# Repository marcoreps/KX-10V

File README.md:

# KX-10V
Temperature controller and 10V buffer for xDevs KX LTZ1000 board

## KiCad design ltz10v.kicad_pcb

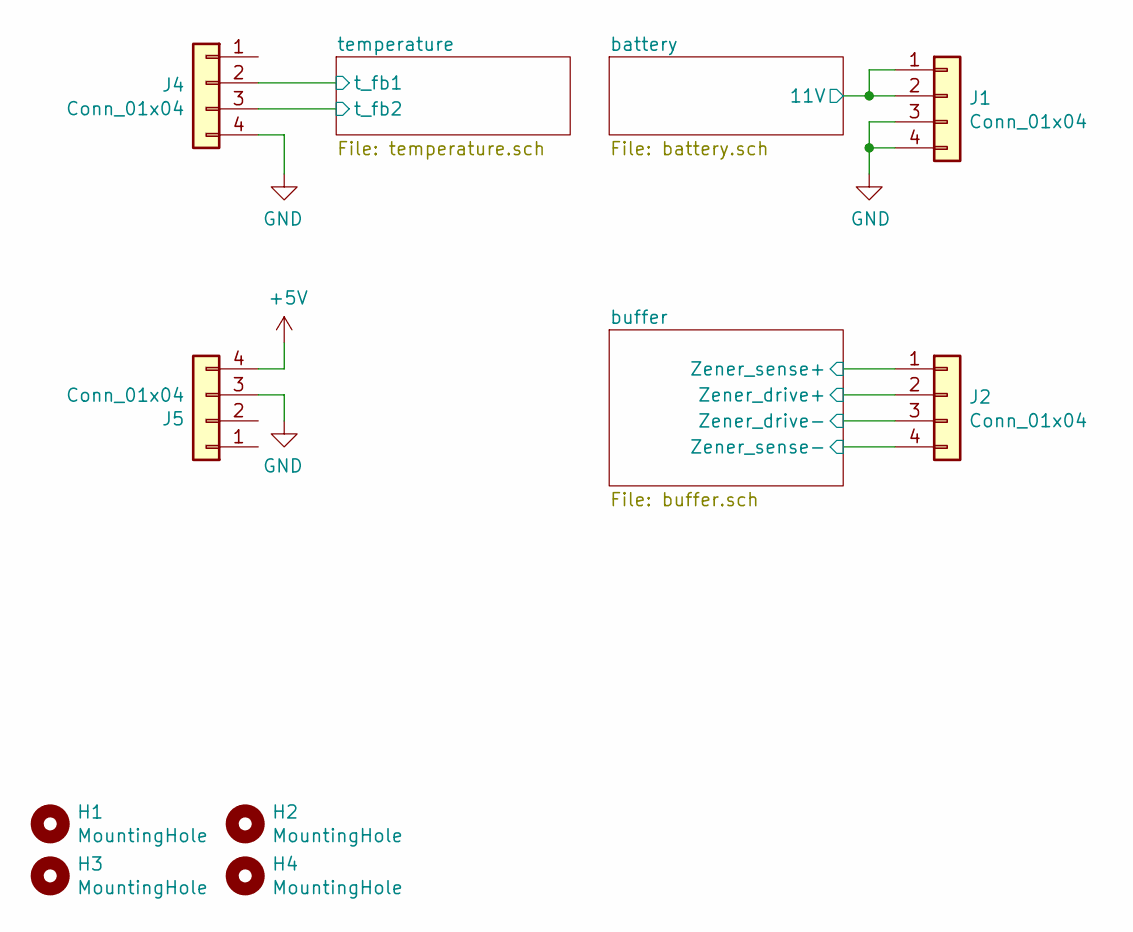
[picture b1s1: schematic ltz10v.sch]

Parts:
H1, H2, H3, H4: MountingHole; MountingHole_3.2mm_M3
J1, J2, J4, J5: Conn_01x04; PinHeader_1x04_P2.54mm_Vertical

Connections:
+5V: J5.4; also elsewhere on the board
/battery/11V: J1.1, J1.2; also elsewhere on the board
/buffer/Zener_drive+: J2.1, J2.2; also elsewhere on the board
/buffer/Zener_drive-: J2.3, J2.4; also elsewhere on the board
/temperature/t_fb1: J4.2; also elsewhere on the board
/temperature/t_fb2: J4.3; also elsewhere on the board
GND: J1.3, J1.4, J4.4, J5.3; also elsewhere on the board

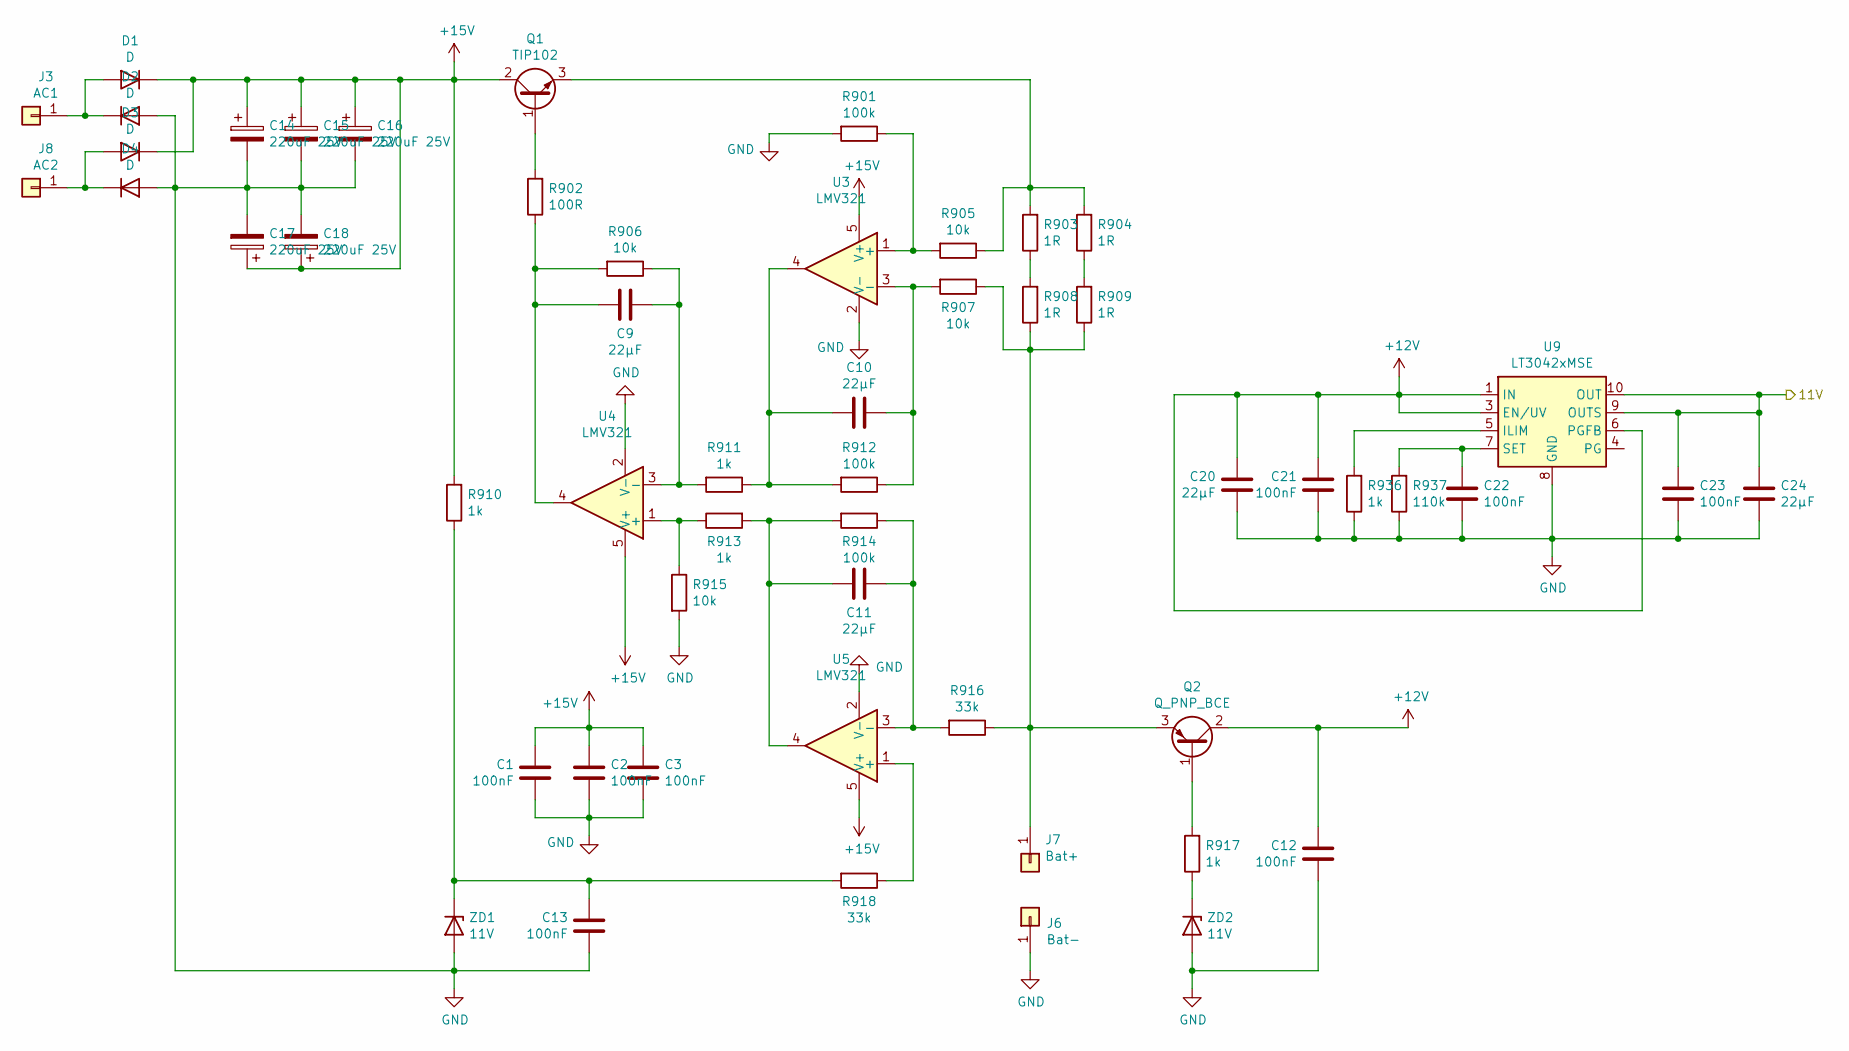
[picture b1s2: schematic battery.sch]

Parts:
C1, C2, C3, C12, C13, C21, C22, C23: 100nF; C_0805_2012Metric; LCSC C49678
C9, C10, C11, C20, C24: 22µF; C_0805_2012Metric; LCSC C45783
C14, C15, C16, C17, C18: 220uF 25V; CP_Elec_6.3x7.7
D1, D2, D3, D4: D; D_SMA; LCSC C8678
J3: AC1; SolderWirePad_1x01_Drill1.5mm
J6: Bat-; SolderWirePad_1x01_Drill1.5mm
J7: Bat+; SolderWirePad_1x01_Drill1.5mm
J8: AC2; SolderWirePad_1x01_Drill1.5mm
Q1: TIP102; TO-220-3_Vertical
Q2: Q_PNP_BCE; SOT-89-3; LCSC C24278
R901, R912, R914: 100k; R_0805_2012Metric; LCSC C17407
R902: 100R; R_0805_2012Metric; LCSC C17408
R903, R904, R908, R909: 1R; R_1206_3216Metric; LCSC C17928
R905, R906, R907, R915: 10k; R_0805_2012Metric; LCSC C17414
R910, R911, R913, R917, R936: 1k; R_0805_2012Metric; LCSC C17513
R916, R918: 33k; R_0805_2012Metric; LCSC C17633
R937: 110k; R_0805_2012Metric; LCSC C17422
U3, U4, U5: LMV321; SOT-23-5; LCSC C7972
U9: LT3042xMSE; MSOP-10-1EP_3x3mm_P0.5mm_EP1.68x1.88mm
ZD1, ZD2: 11V; D_SOD-323

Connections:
+12V: C12.1, C20.2, C21.1, Q2.2 (C), U9.1 (IN), U9.2 (IN), U9.3 (EN/UV), U9.6 (PGFB); also elsewhere on the board
+15V: C1.1, C2.1, C3.1, C14.1, C15.1, C16.1, C17.1, C18.1, D1.1 (K), D3.1 (K), Q1.2 (C), R910.2, U3.5 (V+), U4.5 (V+), U5.5 (V+)
/battery/11V: C23.1, C24.2, U9.9 (OUTS), U9.10 (OUT); also elsewhere on the board
GND: C1.2, C2.2, C3.2, C12.2, C13.2, C14.2, C15.2, C16.2, C17.2, C18.2, C20.1, C21.2, C22.2, C23.2, C24.1, D2.2 (A), D4.2 (A), J6.1, R901.2, R915.2, R936.1, R937.1, U3.2 (V-), U4.2 (V-), U5.2 (V-), U9.8 (GND), U9.11 (GND), ZD1.2 (A), ZD2.2 (A); also elsewhere on the board
unnamed: C9.1, R906.1, R911.2, U4.3 (-)
unnamed: C9.2, R902.1, R906.2, U4.4
unnamed: C10.1, R907.2, R912.1, U3.3 (-)
unnamed: C10.2, R911.1, R912.2, U3.4
unnamed: C11.1, R914.1, R916.2, U5.3 (-)
unnamed: C11.2, R913.2, R914.2, U5.4
unnamed: C13.1, R910.1, R918.2, ZD1.1 (K)
unnamed: C22.1, R937.2, U9.7 (SET)
unnamed: D1.2 (A), D2.1 (K), J3.1
unnamed: D3.2 (A), D4.1 (K), J8.1
unnamed: J7.1, Q2.3 (E), R907.1, R908.1, R909.1, R916.1
unnamed: Q1.1 (B), R902.2
unnamed: Q1.3 (E), R903.2, R904.2, R905.1
unnamed: Q2.1 (B), R917.2
unnamed: R901.1, R905.2, U3.1 (+)
unnamed: R903.1, R908.2
unnamed: R904.1, R909.2
unnamed: R913.1, R915.1, U4.1 (+)
unnamed: R917.1, ZD2.1 (K)
unnamed: R918.1, U5.1 (+)
unnamed: R936.2, U9.5 (ILIM)

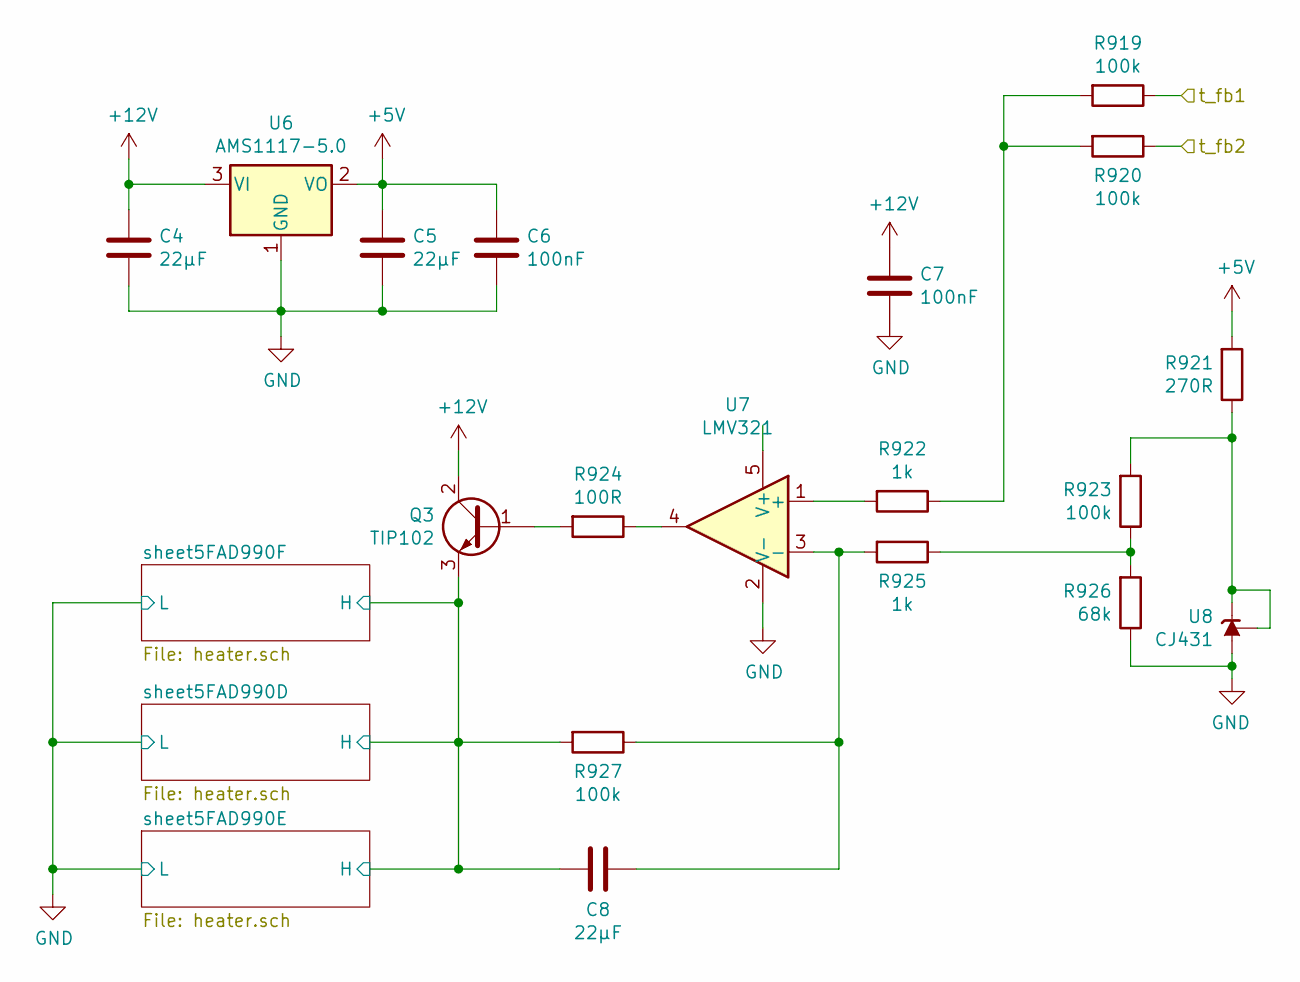
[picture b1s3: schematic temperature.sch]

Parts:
C4, C5, C8: 22µF; C_0805_2012Metric; LCSC C45783
C6, C7: 100nF; C_0805_2012Metric; LCSC C49678
Q3: TIP102; TO-220-3_Vertical
R919, R920, R923, R927: 100k; R_0805_2012Metric; LCSC C17407
R921: 270R; R_0805_2012Metric; LCSC C17590
R922, R925: 1k; R_0805_2012Metric; LCSC C17513
R924: 100R; R_0805_2012Metric; LCSC C17408
R926: 68k; R_0805_2012Metric; LCSC C17801
U6: AMS1117-5.0; SOT-223-3_TabPin2; LCSC C6187
U7: LMV321; SOT-23-5; LCSC C7972
U8: CJ431; SOT-23; LCSC C3113

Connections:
+5V: C5.1, C6.1, R921.2, U6.2 (VO); also elsewhere on the board
+12V: C4.1, C7.1, Q3.2 (C), U6.3 (VI); also elsewhere on the board
/temperature/sheet5FAD990D/H: C8.2, Q3.3 (E), R927.2; also elsewhere on the board
/temperature/t_fb1: R919.1; also elsewhere on the board
/temperature/t_fb2: R920.1; also elsewhere on the board
GND: C4.2, C5.2, C6.2, C7.2, R926.1, U6.1 (GND), U7.2 (V-), U8.3 (A); also elsewhere on the board
unnamed: C8.1, R925.2, R927.1, U7.3 (-)
unnamed: Q3.1 (B), R924.2
unnamed: R919.2, R920.2, R922.1
unnamed: R921.1, R923.2, U8.1 (REF), U8.2 (K)
unnamed: R922.2, U7.1 (+)
unnamed: R923.1, R925.1, R926.2
unnamed: R924.1, U7.4

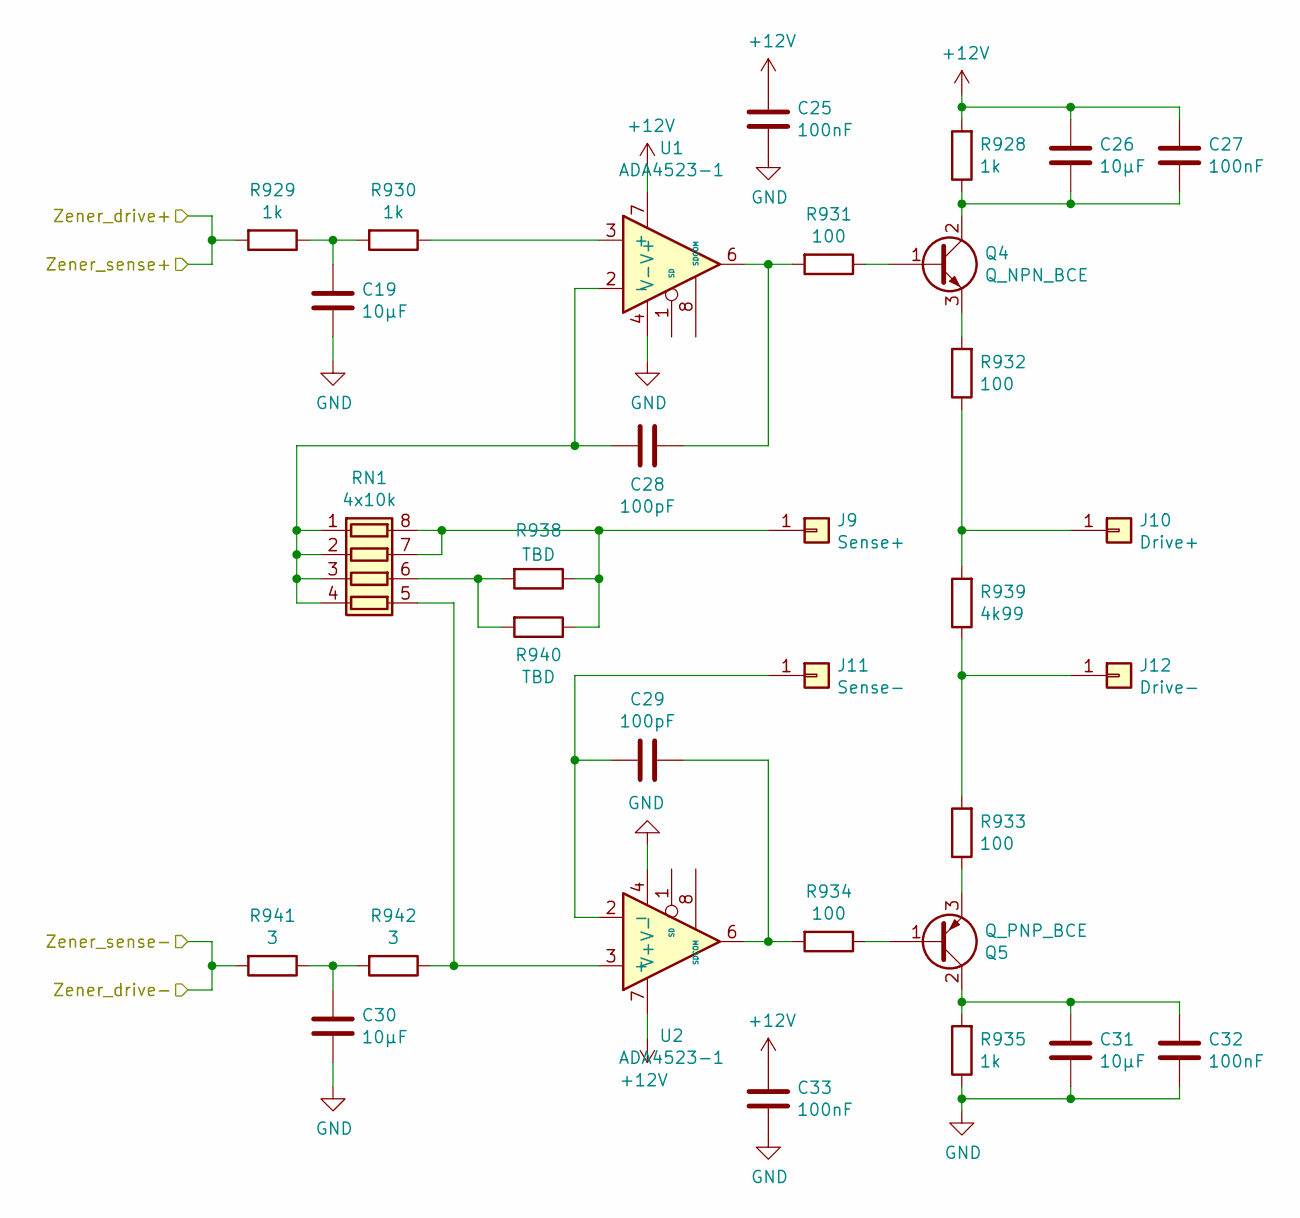
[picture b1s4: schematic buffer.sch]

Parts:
C19, C26, C30, C31: 10µF; C_0805_2012Metric
C25, C27, C32, C33: 100nF; C_0805_2012Metric
C28, C29: 100pF; C_0805_2012Metric
J9: Sense+; SolderWirePad_1x01_Drill0.8mm
J10: Drive+; SolderWirePad_1x01_Drill0.8mm
J11: Sense-; SolderWirePad_1x01_Drill0.8mm
J12: Drive-; SolderWirePad_1x01_Drill0.8mm
Q4: Q_NPN_BCE; SOT-223-3_TabPin2
Q5: Q_PNP_BCE; SOT-223-3_TabPin2
R928, R929, R930, R935: 1k; R_0805_2012Metric
R931, R932, R933, R934: 100; R_0805_2012Metric
R938: TBD; R_0805_2012Metric
R939: 4k99; R_0805_2012Metric
R940: TBD; R_4020_10251Metric_Pad1.65x5.30mm_HandSolder
R941, R942: 3; R_0805_2012Metric
RN1: 4x10k; MSOP-8-1EP_3x3mm_P0.65mm_EP1.68x1.88mm
U1, U2: ADA4523-1; SOIC-8_3.9x4.9mm_P1.27mm

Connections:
+12V: C25.1, C26.1, C27.1, C33.1, R928.2, U1.7 (V+), U2.7 (V+); also elsewhere on the board
/buffer/Zener_drive+: R929.2; also elsewhere on the board
/buffer/Zener_drive-: R941.2; also elsewhere on the board
GND: C19.2, C25.2, C30.2, C31.2, C32.2, C33.2, R935.1, U1.4 (V-), U2.4 (V-); also elsewhere on the board
unnamed: C19.1, R929.1, R930.2
unnamed: C26.2, C27.2, Q4.2 (C), R928.1
unnamed: C28.1, R931.2, U1.6
unnamed: C28.2, RN1.1 (R1.1), RN1.2 (R2.1), RN1.3 (R3.1), RN1.4 (R4.1), U1.2 (-)
unnamed: C29.1, R934.2, U2.6
unnamed: C29.2, J11.1, U2.2 (-)
unnamed: C30.1, R941.1, R942.2
unnamed: J9.1, R938.1, R940.1, RN1.7 (R2.2), RN1.8 (R1.2)
unnamed: J10.1, R932.1, R939.2
unnamed: J12.1, R933.2, R939.1
unnamed: Q4.1 (B), R931.1
unnamed: Q4.3 (E), R932.2
unnamed: Q5.1 (B), R934.1
unnamed: R930.1, U1.3 (+)
unnamed: R938.2, R940.2, RN1.6 (R3.2)
unnamed: R942.1, RN1.5 (R4.2), U2.3 (+)
